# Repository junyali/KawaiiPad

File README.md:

# KawaiiPad

My first macropad that looks quite cute! :3
Designed in KiCAD, Fusion360, and QMK Firmware

## Concept

| Demo             |                      Image                       |
|------------------|:------------------------------------------------:|
| Schematic        |                |
| PCB Design       |              |
| PCB Front Render |  |
| PCB Back Render  |    |
| Case Render      |            |  

## BOM

- 1x SEEED XIAO RP2040
- 9x Cherry MX switches
- 9x White keycaps (include some Hack Club ones please!!)
- 9x 1N4148 Through-hole diodes
- 9x SK6812-MINI LED
- 4x M3x16mm screws
- 4x M3 hex nuts
- 1x KawaiiPad 3D Printed case
- ~~100g of Francium owo~~

## Final thoughts
Honestly, this was a really daunting task considering I have never touched PCB design, and hadn't used Fusion360 for CAD design in at least 4 years. After some motivation from the helpful Hack Club community, I am pretty pleased with the final results :DD

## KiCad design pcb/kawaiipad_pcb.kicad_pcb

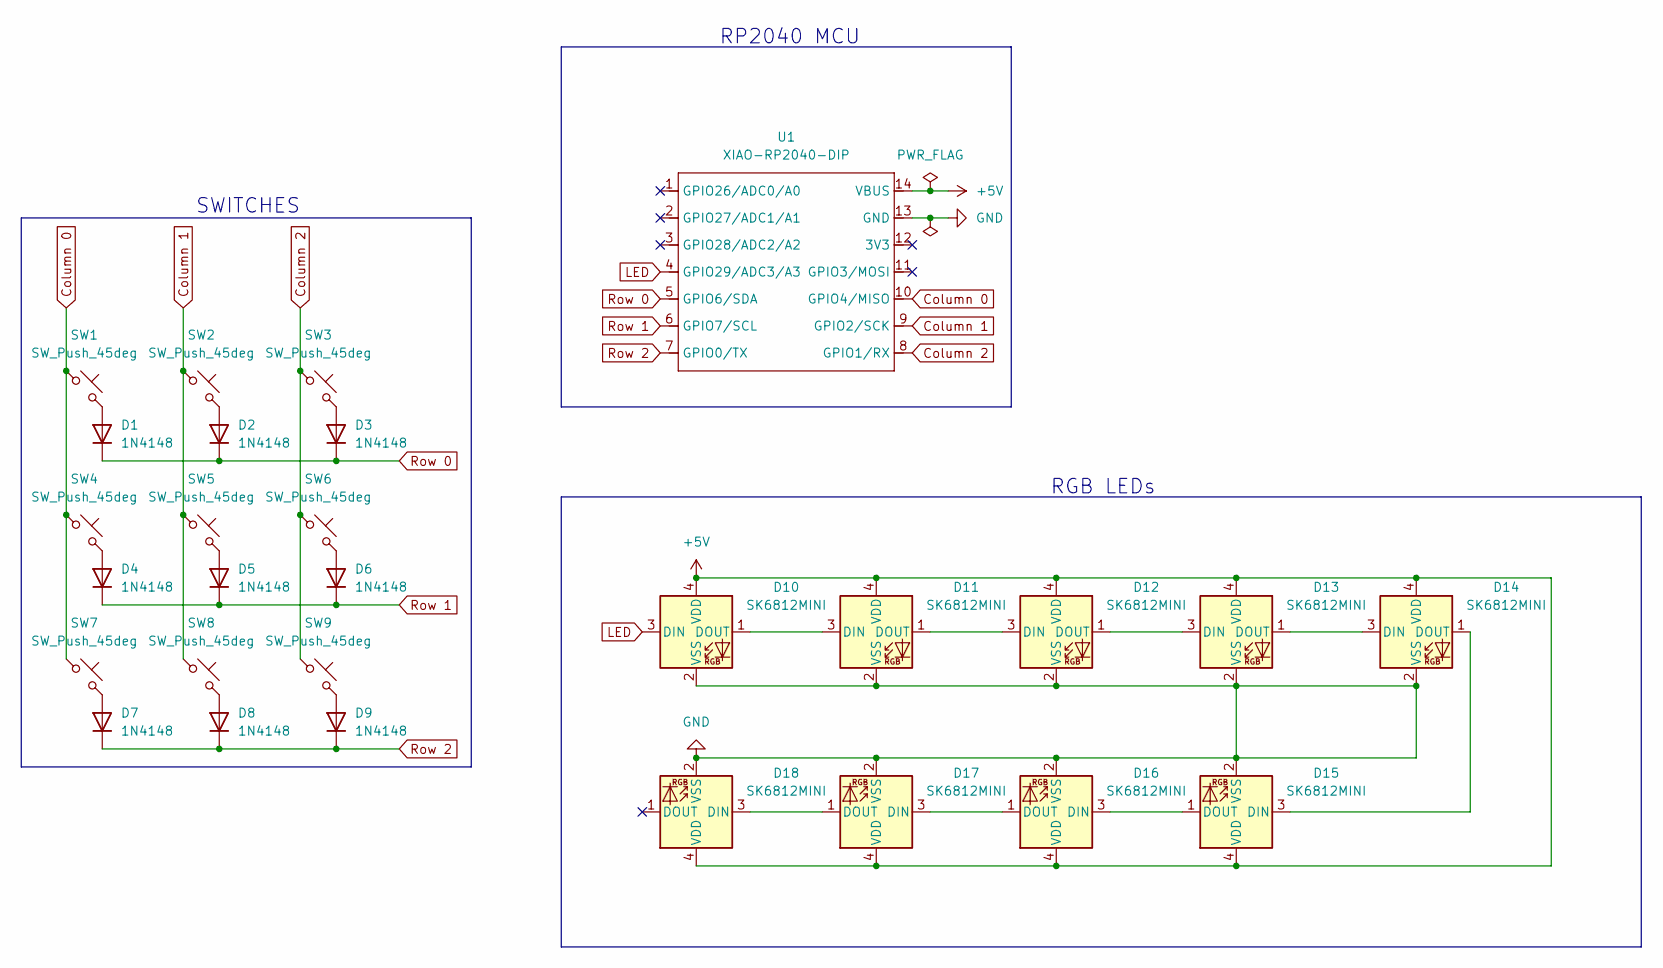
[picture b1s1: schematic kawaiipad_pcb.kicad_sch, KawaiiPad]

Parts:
D1, D2, D3, D4, D5, D6, D7, D8, D9: 1N4148; Diode-Hybrid-Dual
D10, D11, D12, D13, D14, D15, D16, D17, D18: SK6812MINI; LED_SK6812MINI_PLCC4_3.5x3.5mm_P1.75mm
SW1, SW2, SW3, SW4, SW5, SW6, SW7, SW8, SW9: SW_Push_45deg; SW_Cherry_MX_1.00u_PCB
U1: XIAO-RP2040-DIP

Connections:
+5V: D10.4 (VDD), D11.4 (VDD), D12.4 (VDD), D13.4 (VDD), D14.4 (VDD), D15.4 (VDD), D16.4 (VDD), D17.4 (VDD), D18.4 (VDD), U1.14 (VBUS)
Column 0: SW1.1, SW4.1, SW7.1, U1.10 (GPIO4/MISO)
Column 1: SW2.1, SW5.1, SW8.1, U1.9 (GPIO2/SCK)
Column 2: SW3.1, SW6.1, SW9.1, U1.8 (GPIO1/RX)
GND: D10.2 (VSS), D11.2 (VSS), D12.2 (VSS), D13.2 (VSS), D14.2 (VSS), D15.2 (VSS), D16.2 (VSS), D17.2 (VSS), D18.2 (VSS), U1.13 (GND)
LED: D10.3 (DIN), U1.4 (GPIO29/ADC3/A3)
unnamed: D1.2 (A), SW1.2
unnamed: D2.2 (A), SW2.2
unnamed: D3.2 (A), SW3.2
unnamed: D4.2 (A), SW4.2
unnamed: D5.2 (A), SW5.2
unnamed: D6.2 (A), SW6.2
unnamed: D7.2 (A), SW7.2
unnamed: D8.2 (A), SW8.2
unnamed: D9.2 (A), SW9.2
unnamed: D10.1 (DOUT), D11.3 (DIN)
unnamed: D11.1 (DOUT), D12.3 (DIN)
unnamed: D12.1 (DOUT), D13.3 (DIN)
unnamed: D13.1 (DOUT), D14.3 (DIN)
unnamed: D14.1 (DOUT), D15.3 (DIN)
unnamed: D15.1 (DOUT), D16.3 (DIN)
unnamed: D16.1 (DOUT), D17.3 (DIN)
unnamed: D17.1 (DOUT), D18.3 (DIN)
Row 0: D1.1 (K), D2.1 (K), D3.1 (K), U1.5 (GPIO6/SDA)
Row 1: D4.1 (K), D5.1 (K), D6.1 (K), U1.6 (GPIO7/SCL)
Row 2: D7.1 (K), D8.1 (K), D9.1 (K), U1.7 (GPIO0/TX)

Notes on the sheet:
SWITCHES
RGB LEDs
RP2040 MCU

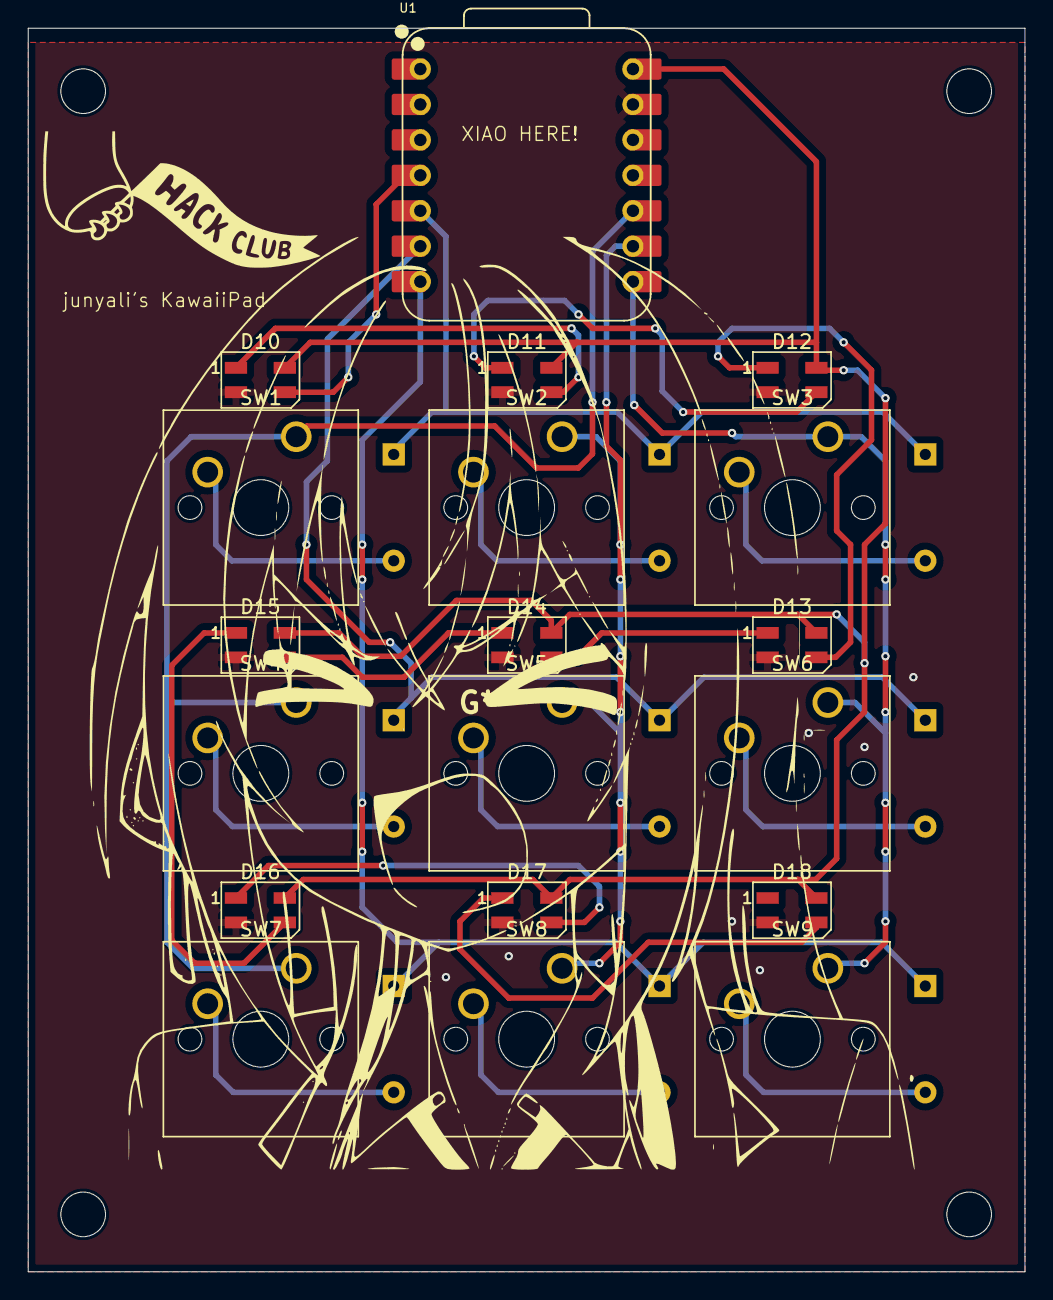
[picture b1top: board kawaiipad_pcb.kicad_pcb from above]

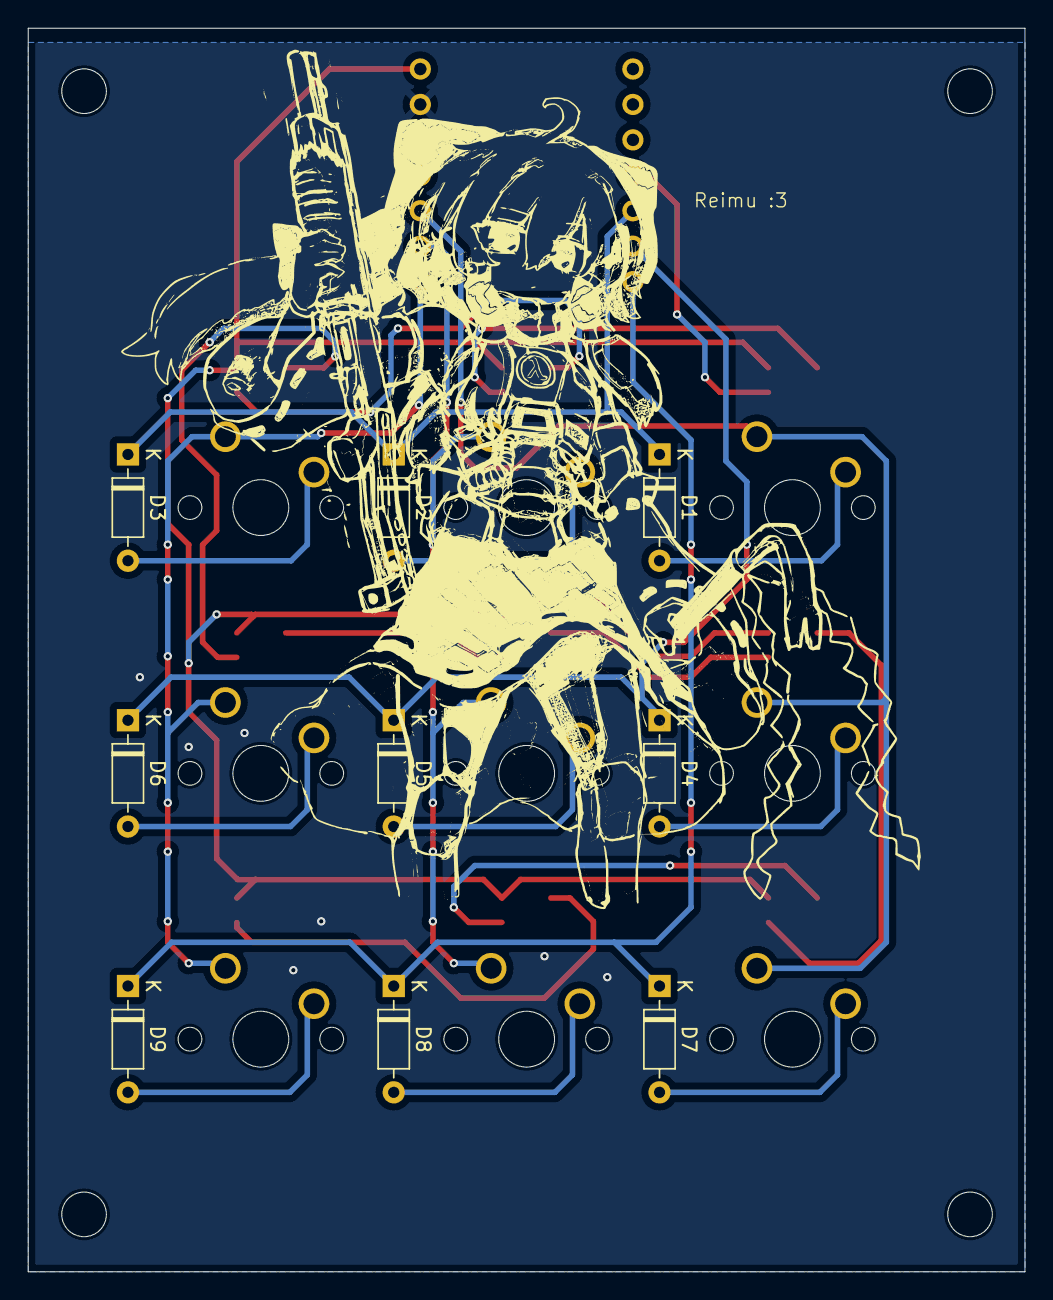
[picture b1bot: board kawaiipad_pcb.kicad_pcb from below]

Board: 2 copper layers, 71.4 x 89.1 mm, 28 parts (9 on the bottom side), 26 nets.

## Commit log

2025-02-10 Initial Commit with PCB
2025-02-10 Add Diode 1N418, remove accidental extra LEDs, assign footprints
2025-02-12 clear pcb, fix schematic
2025-02-12 clear pcb
2025-02-13 finish PCB wiring
2025-02-14 replace diodes with actual footprint
2025-02-14 rearrange led on pcb
2025-02-14 add scotto library, remove unecessary diode lib
2025-02-14 add leds, edge cuts, properly measured
2025-02-15 redesign pcb w/o gnd
2025-02-15 add groundpour
2025-02-15 add silkscreen art
2025-02-15 update pcb text + add ssart
2025-02-15 generate gerbers
2025-02-15 add cad files
2025-02-15 move production files
2025-02-15 Add case stl file to production
2025-02-15 add firmware
2025-02-15 Add README.md
